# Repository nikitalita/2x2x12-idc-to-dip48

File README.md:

# 2x2x12 header to DIP48 adapter

This adapter is designed to be used with test clips that have 2.54mm headers. 
Straight 1:1 translation.

WARNING: COMPLETELY UNTESTED

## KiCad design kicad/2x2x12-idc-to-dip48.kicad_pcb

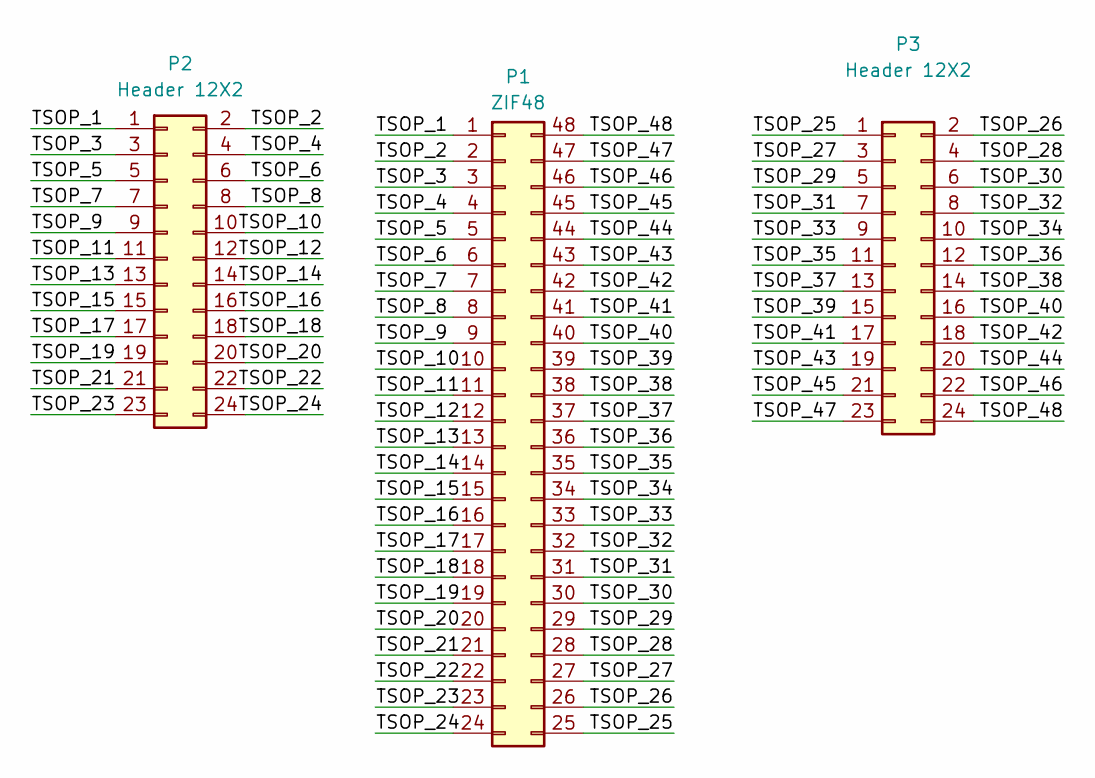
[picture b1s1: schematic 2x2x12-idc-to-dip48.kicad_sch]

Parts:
P1: ZIF48; P1
P2: Header 12X2; P2
P3: Header 12X2; P3

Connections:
/TSOP_1: P1.1, P2.1
/TSOP_2: P1.2, P2.2
/TSOP_3: P1.3, P2.3
/TSOP_4: P1.4, P2.4
/TSOP_5: P1.5, P2.5
/TSOP_6: P1.6, P2.6
/TSOP_7: P1.7, P2.7
/TSOP_8: P1.8, P2.8
/TSOP_9: P1.9, P2.9
/TSOP_10: P1.10, P2.10
/TSOP_11: P1.11, P2.11
/TSOP_12: P1.12, P2.12
/TSOP_13: P1.13, P2.13
/TSOP_14: P1.14, P2.14
/TSOP_15: P1.15, P2.15
/TSOP_16: P1.16, P2.16
/TSOP_17: P1.17, P2.17
/TSOP_18: P1.18, P2.18
/TSOP_19: P1.19, P2.19
/TSOP_20: P1.20, P2.20
/TSOP_21: P1.21, P2.21
/TSOP_22: P1.22, P2.22
/TSOP_23: P1.23, P2.23
/TSOP_24: P1.24, P2.24
/TSOP_25: P1.25, P3.1
/TSOP_26: P1.26, P3.2
/TSOP_27: P1.27, P3.3
/TSOP_28: P1.28, P3.4
/TSOP_29: P1.29, P3.5
/TSOP_30: P1.30, P3.6
/TSOP_31: P1.31, P3.7
/TSOP_32: P1.32, P3.8
/TSOP_33: P1.33, P3.9
/TSOP_34: P1.34, P3.10
/TSOP_35: P1.35, P3.11
/TSOP_36: P1.36, P3.12
/TSOP_37: P1.37, P3.13
/TSOP_38: P1.38, P3.14
/TSOP_39: P1.39, P3.15
/TSOP_40: P1.40, P3.16
/TSOP_41: P1.41, P3.17
/TSOP_42: P1.42, P3.18
/TSOP_43: P1.43, P3.19
/TSOP_44: P1.44, P3.20
/TSOP_45: P1.45, P3.21
/TSOP_46: P1.46, P3.22
/TSOP_47: P1.47, P3.23
/TSOP_48: P1.48, P3.24

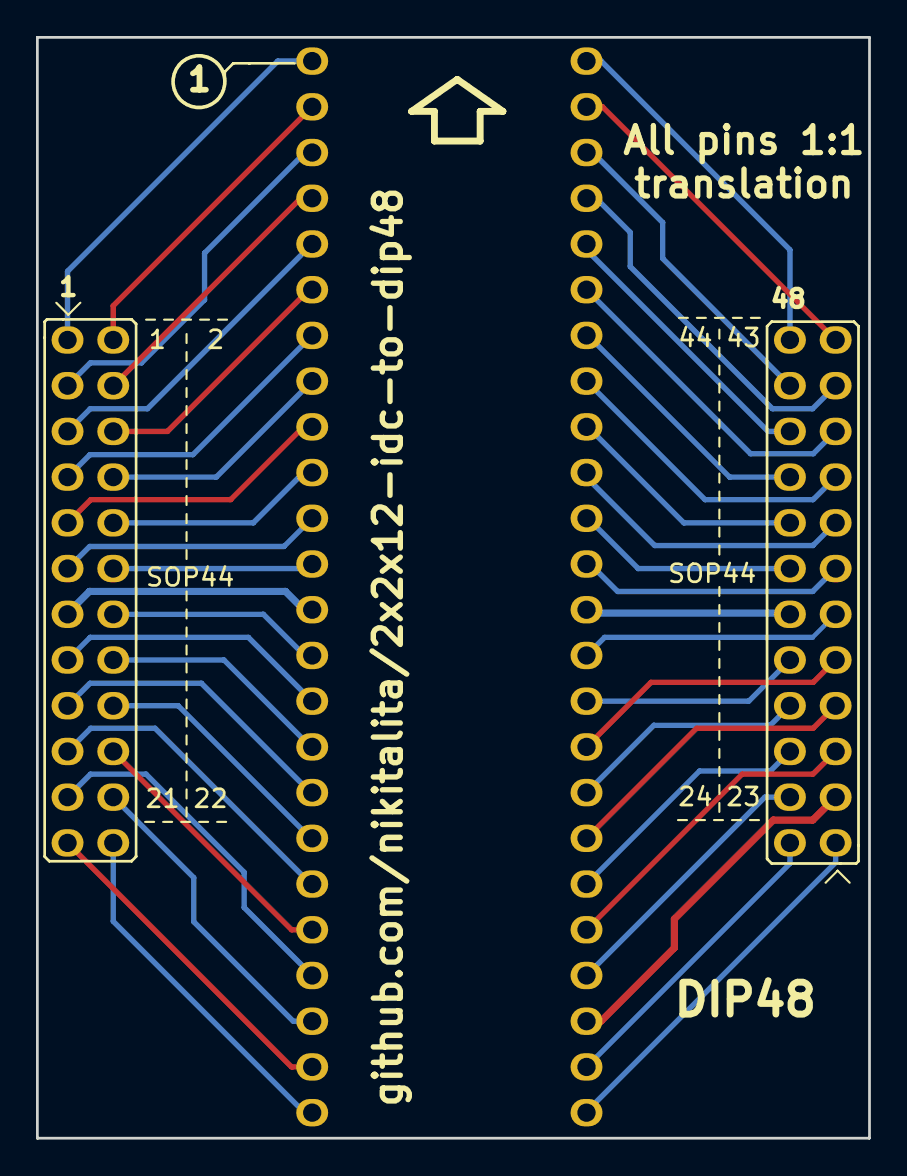
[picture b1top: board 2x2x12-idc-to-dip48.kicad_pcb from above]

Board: 2 copper layers, 46.2 x 61.2 mm, 3 parts (1 on the bottom side), 48 nets.
